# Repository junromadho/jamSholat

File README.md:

# jamSholat
بسم الله الرحمن الرحيم  

Project jam sholat untuk led modul P4.75 dengan menggunakan board berbasis STM32, free to share!

Note: 
Project ini didedikasikan sepenuhnya untuk keperluan amal, silakan memanfaatkan, menyebarkan, dan mengembangkannya. 
Adapun jika anda berniat untuk memanfaatkannya untuk keperluan komersial, harap sisihkan keuntungannya untuk pengembangan lebih lanjut lalu sebarkan ulang pengetahuan tersebut, semoga saja keuntungan yang didapat tidak berhenti hingga rupiah yang terkumpul. tetapi ada keuntungan akhirat yang juga ikut kita tabung.. 

Project ini terdiri dari 3 bagian hardware, software, dan tools
***
## Hardware
Mikrokontroller core yang dipakai adalah varian dari STM32 Bluepill atau Blackpill(belom tested).
Saya biasa memakai varian STM32F103C8T6 dengan papan berwarna biru. 

Dalam kontroler board utama (file: Digital_Praytime_Display_P4.75_v0.9.brd) terdiri dari:
* soket mikrokontroler
* soket untuk HUB08
* soket baterai RTC 
* interface untuk rotary encoder
* interface untuk serial
* interface untuk buzzer
* terminal power

Pada board eksternal (file: External_Battery.brd dan Encoder.brd) terdiri dari:
* soket baterai 
* tombol rotary encoder

board eksternal berfungsi sebagai papan expansi untuk jam sholat yang menggunakan frame tertutup, sehingga board ini bisa diakses diluar 

## Software
Software yang dipakai adalah arduino dengan menggunakan tambahan *hardware* STM32 dari [Arduino STM32](https://github.com/rogerclarkmelbourne/Arduino_STM32). Untuk library saya memakai HUB08 dan RTClock.

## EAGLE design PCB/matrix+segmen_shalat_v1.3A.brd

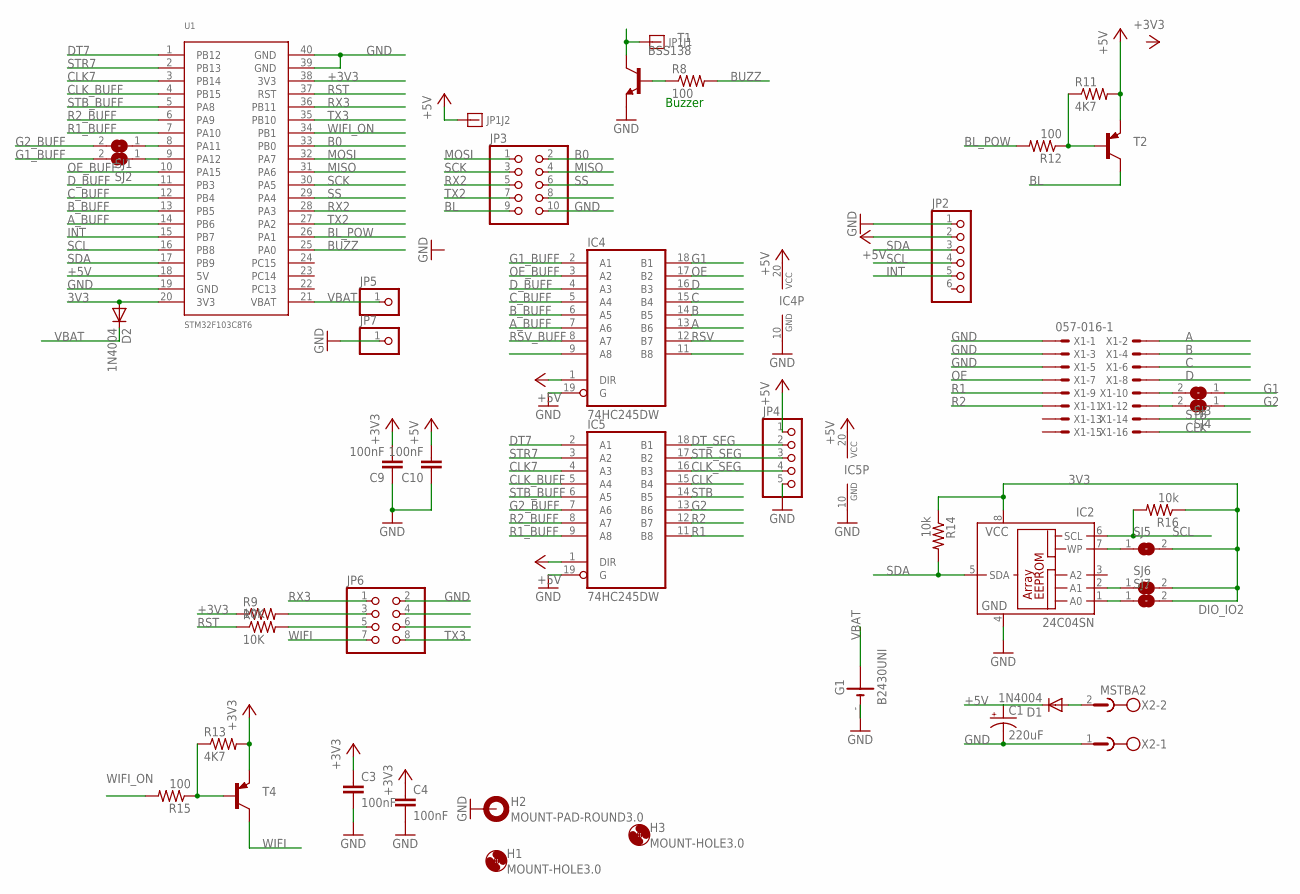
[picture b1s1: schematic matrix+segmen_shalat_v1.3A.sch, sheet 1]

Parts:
C1: 220uF; E3,5-8
C3, C4, C9, C10: 100nF; C0805
D1, D2: 1N4004; DO41-10
G1: B2430UNI
H1, H3: MOUNT-HOLE3.0; 3,0
H2: MOUNT-PAD-ROUND3.0; 3,0-PAD
IC2: 24C04SN; SO-08
IC4, IC5: 74HC245DW; SO20W
JP1: CON2-3.81
JP2: PINHD-1X6; 1X06
JP3: PINHD-2X5; 2X05
JP4: PINHD-1X5; 1X05
JP5, JP7: PINHD-1X1; 1X01
JP6: PINHD-2X4; 2X04
R7, R9: 10K; R0805
R8, R12, R15: 100; R0805
R11, R13: 4K7; R0805
R14, R16: 10k; R0805
SJ1, SJ2, SJ3, SJ4, SJ5, SJ6, SJ7: SJ
T1: BSS138; SOT23-BEC
T2, T4: -PNP-TO126V; TO126V
U1: STM32F103C8T6; STM32F103
X1: 057-016-1
X2: MSTBA2

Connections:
3V3: D2.A, IC2.8 (VCC), R14.1, R16.1, SJ5.2, SJ6.2, SJ7.2, U1.20 (3V3)
+3V3: C3.1, C4.1, C9.2, R9.1, R13.2, T4.1 (E), U1.38 (3V3)
+5V: C1.+, C10.2, D1.C, IC4.1 (DIR), IC4.20 (VCC), IC5.1 (DIR), IC5.20 (VCC), JP1.2, JP2.2, JP4.1, R11.2, T2.1 (E), U1.18 (5V)
A: IC4.13 (B6), X1.2
A_BUFF: IC4.7 (A6), U1.14 (PB6)
B: IC4.14 (B5), X1.4
B0: JP3.2, U1.33 (PB0)
BL: JP3.9, T2.2 (C)
BL_POW: R12.2, U1.26 (PA1)
BUZZ: R8.2, U1.25 (PA0)
B_BUFF: IC4.6 (A5), U1.13 (PB5)
C: IC4.15 (B4), X1.6
CLK: IC5.15 (B4), X1.16
CLK7: IC5.4 (A3), U1.3 (PB14)
CLK_BUFF: IC5.5 (A4), U1.4 (PB15)
CLK_SEG: IC5.16 (B3), JP4.4
C_BUFF: IC4.5 (A4), U1.12 (PB4)
D: IC4.16 (B3), X1.8
DT7: IC5.2 (A1), U1.1 (PB12)
DT_SEG: IC5.18 (B1), JP4.2
D_BUFF: IC4.4 (A3), U1.11 (PB3)
G1: IC4.18 (B1), SJ3.1
G1_BUFF: IC4.2 (A1), SJ2.2
G2: IC5.13 (B6), SJ4.1
G2_BUFF: IC5.7 (A6), SJ1.2
GND: C1.-, C3.2, C4.2, C9.1, C10.1, G1.-, G1.-@1 (-), H2.B3,0, IC2.4 (GND), IC4.10 (GND), IC4.19 (G), IC5.10 (GND), IC5.19 (G), JP2.1, JP3.10, JP4.5, JP6.2, JP7.1, T1.E, U1.19 (GND), U1.39 (GND), U1.40 (GND), X1.1, X1.3, X1.5, X2.1
INT: JP2.5, U1.15 (PB7)
MISO: JP3.4, U1.31 (PA6)
MOSI: JP3.1, U1.32 (PA7)
unnamed: R11.1, R12.1, T2.3 (B)
unnamed: R8.1, T1.B
unnamed: JP1.1, T1.C
unnamed: JP6.3, R9.2
unnamed: IC2.2 (A1), SJ6.1
unnamed: R13.1, R15.1, T4.3 (B)
unnamed: SJ1.1, U1.8 (PA11)
unnamed: SJ2.1, U1.9 (PA12)
unnamed: SJ4.2, X1.12
unnamed: SJ3.2, X1.10
unnamed: IC2.1 (A0), SJ7.1
unnamed: JP6.5, R7.2
unnamed: D1.A, X2.2
unnamed: IC2.7 (WP), SJ5.1
OE: IC4.17 (B2), X1.7
OE_BUFF: IC4.3 (A2), U1.10 (PA15)
R1: IC5.11 (B8), X1.9
R1_BUFF: IC5.9 (A8), U1.7 (PA10)
R2: IC5.12 (B7), X1.11
R2_BUFF: IC5.8 (A7), U1.6 (PA9)
RST: R7.1, U1.37 (RST)
RSV: IC4.12 (B7)
RSV_BUFF: IC4.8 (A7)
RX2: JP3.5, U1.28 (PA3)
RX3: JP6.1, U1.36 (PB11)
SCK: JP3.3, U1.30 (PA5)
SCL: IC2.6 (SCL), JP2.4, R16.2, U1.16 (PB8)
SDA: IC2.5 (SDA), JP2.3, R14.2, U1.17 (PB9)
SS: JP3.6, U1.29 (PA4)
STB: IC5.14 (B5), X1.14
STB_BUFF: IC5.6 (A5), U1.5 (PA8)
STR7: IC5.3 (A2), U1.2 (PB13)
STR_SEG: IC5.17 (B2), JP4.3
TX2: JP3.7, U1.27 (PA2)
TX3: JP6.8, U1.35 (PB10)
VBAT: D2.C, G1.+@4 (+), JP5.1, U1.21 (VBAT)
WIFI: JP6.7, T4.2 (C)
WIFI_ON: R15.2, U1.34 (PB1)

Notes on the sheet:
Buzzer

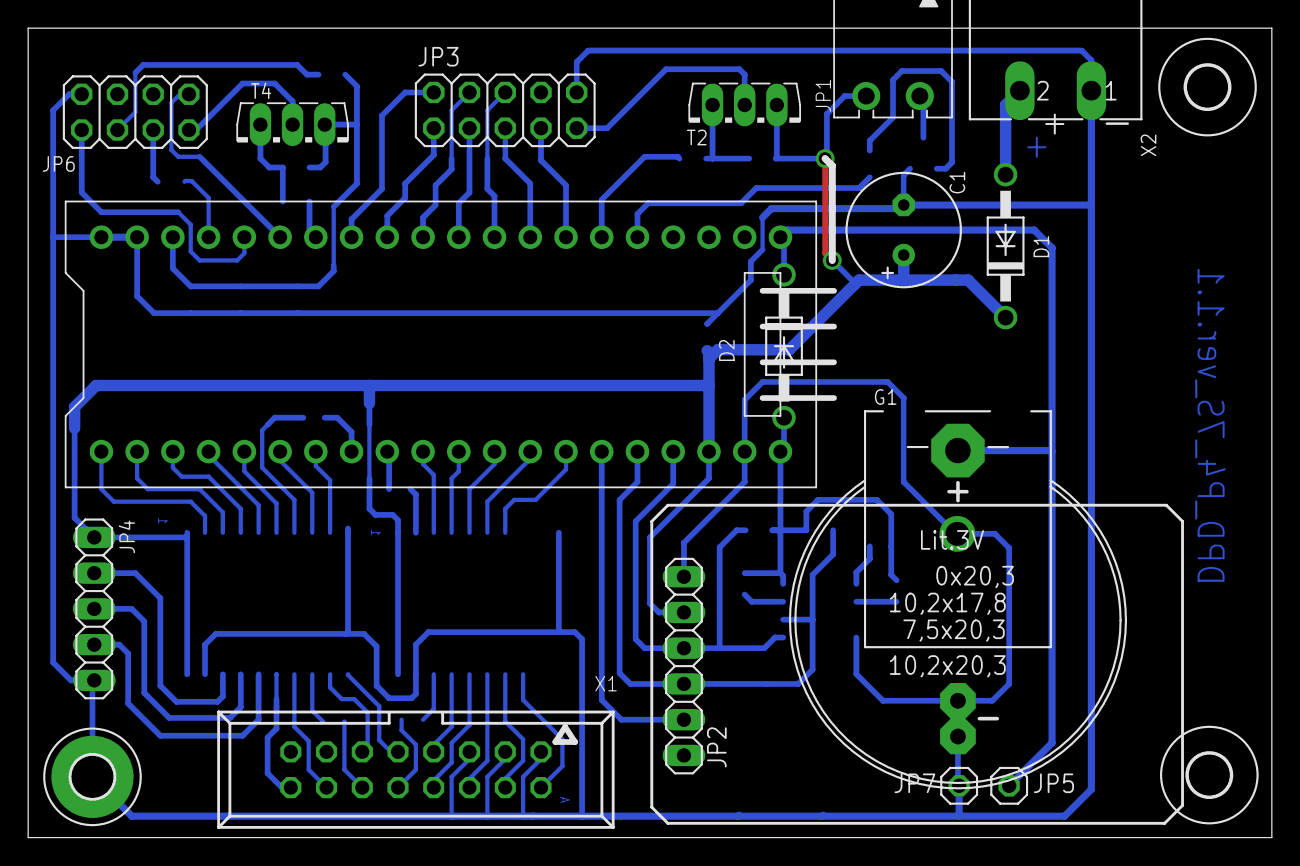
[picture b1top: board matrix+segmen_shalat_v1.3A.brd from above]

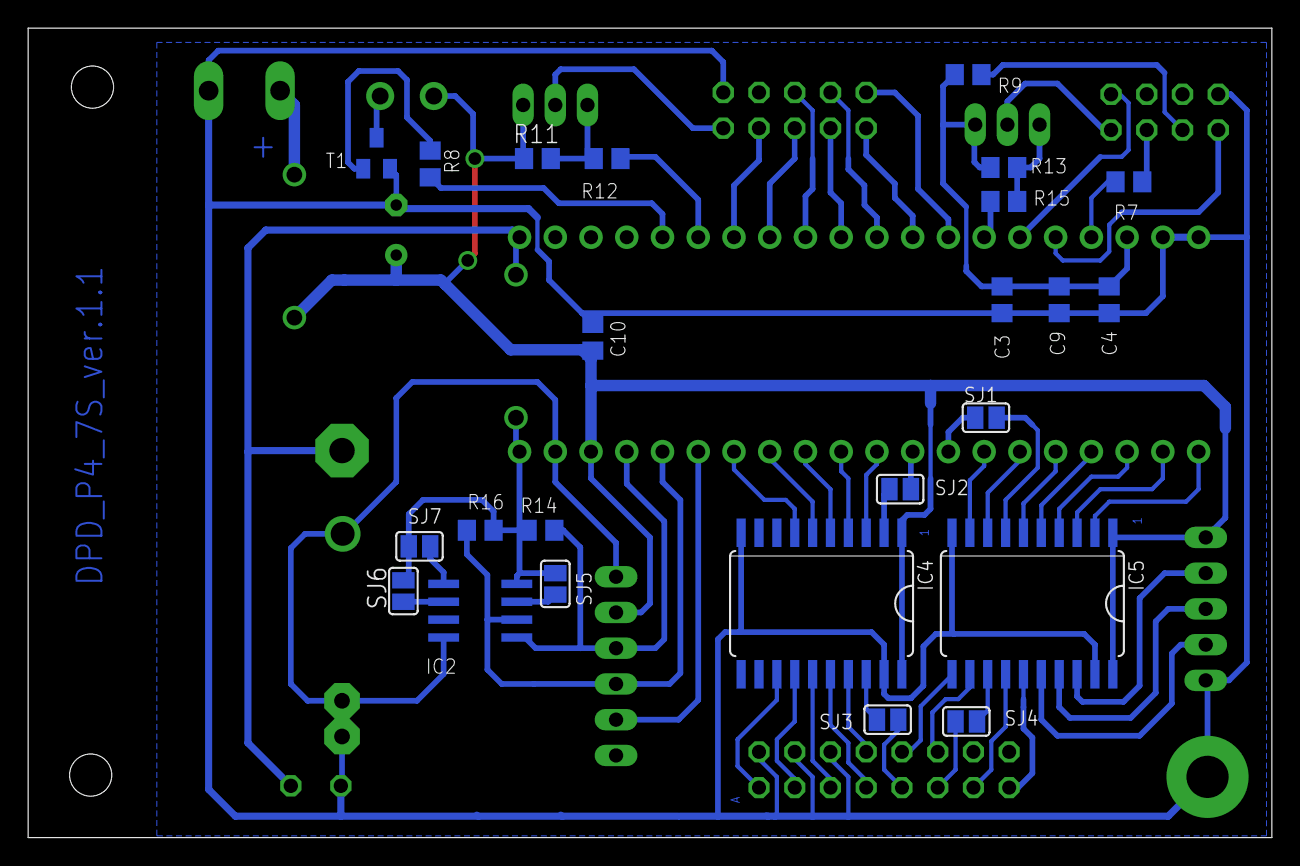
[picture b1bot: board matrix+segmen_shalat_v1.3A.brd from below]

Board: 2 copper layers, 88.4 x 57.5 mm, 43 parts (24 on the bottom side), 65 nets.

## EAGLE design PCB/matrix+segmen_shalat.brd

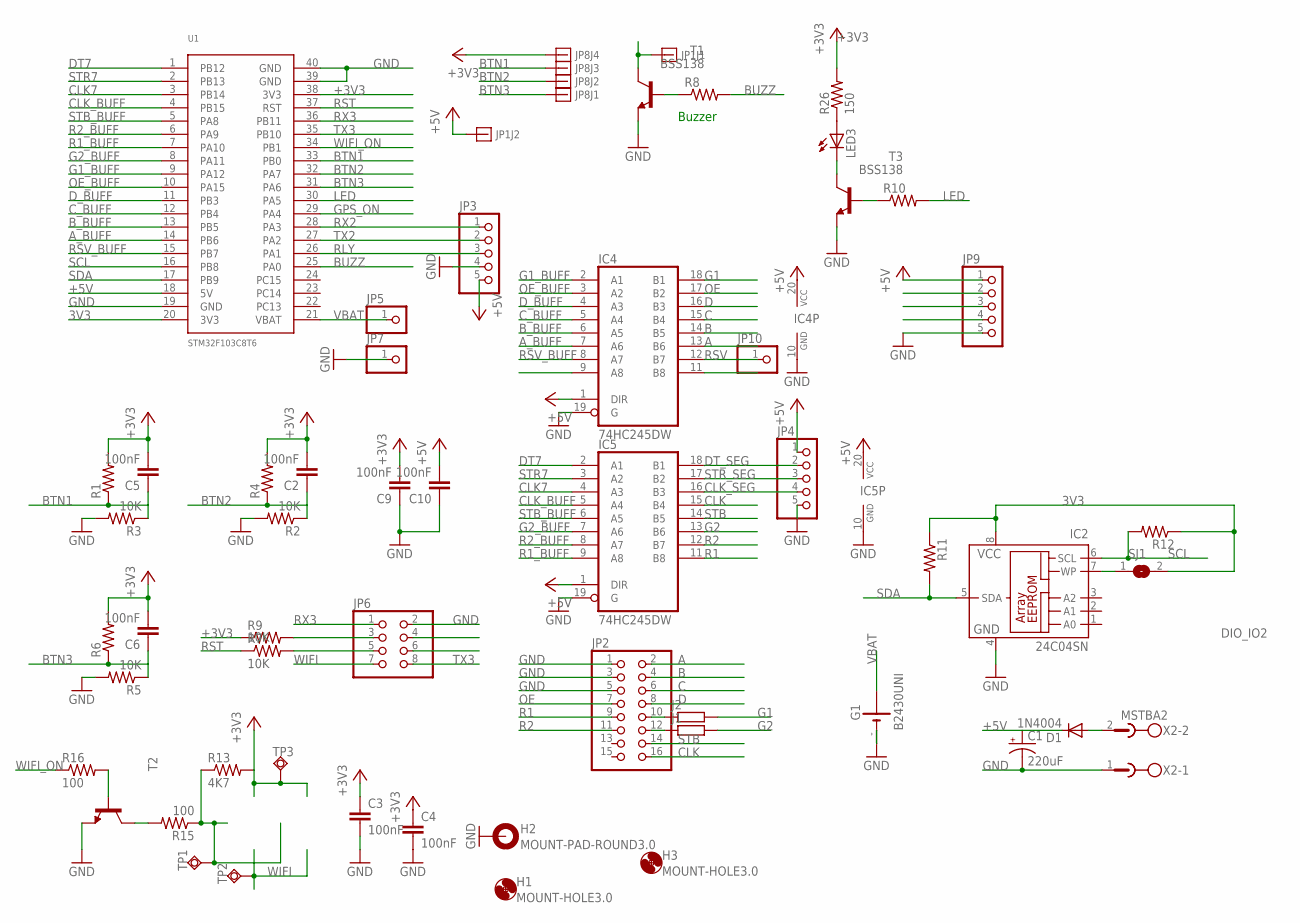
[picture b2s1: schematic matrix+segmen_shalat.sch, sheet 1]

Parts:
C1: 220uF; E3,5-8
C2, C3, C4, C5, C6, C9, C10: 100nF; C0805
D1: 1N4004; DO41-10
G1: B2430UNI
H1, H3: MOUNT-HOLE3.0; 3,0
H2: MOUNT-PAD-ROUND3.0; 3,0-PAD
IC2: 24C04SN; SO-08
IC4, IC5: 74HC245DW; SO20W
J1, J2: R-EU_R0402; R0402
JP1: CON2-3.81
JP2: PINHD-2X8; 2X08
JP3, JP4, JP9: PINHD-1X5; 1X05
JP5, JP7, JP10: PINHD-1X1; 1X01
JP6: PINHD-2X4; 2X04
JP8: CON4-3.81
LED3: LED3MM
R1, R4, R6: R-US_0204/2V; 0204V
R2, R3, R5: 10K; M0805
R7, R9: 10K; R0805
R8, R10, R11, R12: R-US_R0805; R0805
R13: 4K7; R0805
R15, R16: 100; R0805
R26: 150; R0805
SJ1: SJ
T1, T3: BSS138; SOT23-BEC
T2: MMBT2222ALT1-NPN-SOT23-BEC; SOT23-BEC
TP1, TP2, TP3: TPSQPAD1-13Y; P1-13Y
U1: STM32F103C8T6; STM32F103
X2: MSTBA2

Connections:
3V3: IC2.8 (VCC), R11.1, R12.1, SJ1.2, U1.20 (3V3)
+3V3: C2.2, C3.1, C4.1, C5.2, C6.2, C9.2, JP8.4, R1.2, R4.2, R6.2, R9.1, R13.2, R26.2, TP3.TP, U1.38 (3V3)
+5V: C1.+, C10.2, D1.C, IC4.1 (DIR), IC4.20 (VCC), IC5.1 (DIR), IC5.20 (VCC), JP1.2, JP3.5, JP4.1, JP9.1, U1.18 (5V)
A: IC4.13 (B6), JP2.2
A_BUFF: IC4.7 (A6), U1.14 (PB6)
B: IC4.14 (B5), JP2.4
BTN1: C5.1, JP8.3, R1.1, R3.1, U1.33 (PB0)
BTN2: C2.1, JP8.2, R2.1, R4.1, U1.32 (PA7)
BTN3: C6.1, JP8.1, R5.1, R6.1, U1.31 (PA6)
BUZZ: R8.2, U1.25 (PA0)
B_BUFF: IC4.6 (A5), U1.13 (PB5)
C: IC4.15 (B4), JP2.6
CLK: IC5.15 (B4), JP2.16
CLK7: IC5.4 (A3), U1.3 (PB14)
CLK_BUFF: IC5.5 (A4), U1.4 (PB15)
CLK_SEG: IC5.16 (B3), JP4.4
C_BUFF: IC4.5 (A4), U1.12 (PB4)
D: IC4.16 (B3), JP2.8
DT7: IC5.2 (A1), U1.1 (PB12)
DT_SEG: IC5.18 (B1), JP4.2
D_BUFF: IC4.4 (A3), U1.11 (PB3)
G1: IC4.18 (B1), J2.2
G1_BUFF: IC4.2 (A1), U1.9 (PA12)
G2: IC5.13 (B6), J1.2
G2_BUFF: IC5.7 (A6), U1.8 (PA11)
GND: C1.-, C3.2, C4.2, C9.1, C10.1, G1.-, G1.-@1 (-), H2.B3,0, IC2.4 (GND), IC4.10 (GND), IC4.19 (G), IC5.10 (GND), IC5.19 (G), JP2.1, JP2.3, JP2.5, JP3.4, JP4.5, JP6.2, JP7.1, JP9.5, R2.2, R3.2, R5.2, T1.E, T2.E, T3.E, U1.19 (GND), U1.39 (GND), U1.40 (GND), X2.1
GPS_ON: U1.29 (PA4)
LED: R10.2, U1.30 (PA5)
unnamed: J1.1, JP2.12
unnamed: LED3.K (C), T3.C
unnamed: R10.1, T3.B
unnamed: R8.1, T1.B
unnamed: JP1.1, T1.C
unnamed: JP6.3, R9.2
unnamed: J2.1, JP2.10
unnamed: R13.1, R15.1, TP1.TP
unnamed: R15.2, T2.C
unnamed: JP6.5, R7.2
unnamed: R16.2, T2.B
unnamed: LED3.A, R26.1
unnamed: D1.A, X2.2
unnamed: IC2.7 (WP), SJ1.1
OE: IC4.17 (B2), JP2.7
OE_BUFF: IC4.3 (A2), U1.10 (PA15)
R1: IC5.11 (B8), JP2.9
R1_BUFF: IC5.9 (A8), U1.7 (PA10)
R2: IC5.12 (B7), JP2.11
R2_BUFF: IC5.8 (A7), U1.6 (PA9)
RLY: JP3.3, U1.26 (PA1)
RST: R7.1, U1.37 (RST)
RSV: IC4.12 (B7), JP10.1
RSV_BUFF: IC4.8 (A7), U1.15 (PB7)
RX2: JP3.1, U1.28 (PA3)
RX3: JP6.1, U1.36 (PB11)
SCL: IC2.6 (SCL), R12.2, U1.16 (PB8)
SDA: IC2.5 (SDA), R11.2, U1.17 (PB9)
STB: IC5.14 (B5), JP2.14
STB_BUFF: IC5.6 (A5), U1.5 (PA8)
STR7: IC5.3 (A2), U1.2 (PB13)
STR_SEG: IC5.17 (B2), JP4.3
TX2: JP3.2, U1.27 (PA2)
TX3: JP6.8, U1.35 (PB10)
VBAT: G1.+@4 (+), JP5.1, U1.21 (VBAT)
WIFI: JP6.7, TP2.TP
WIFI_ON: R16.1, U1.34 (PB1)

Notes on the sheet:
Buzzer

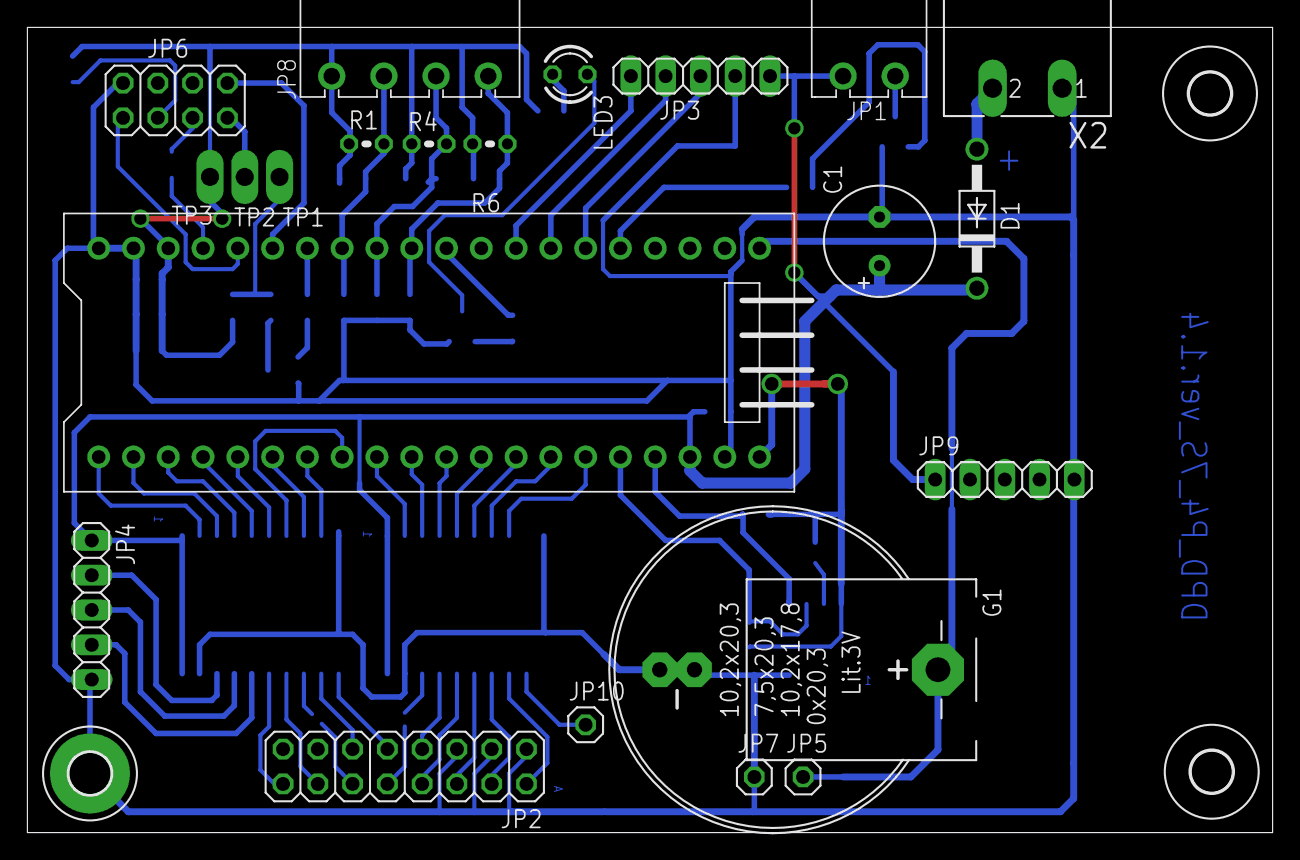
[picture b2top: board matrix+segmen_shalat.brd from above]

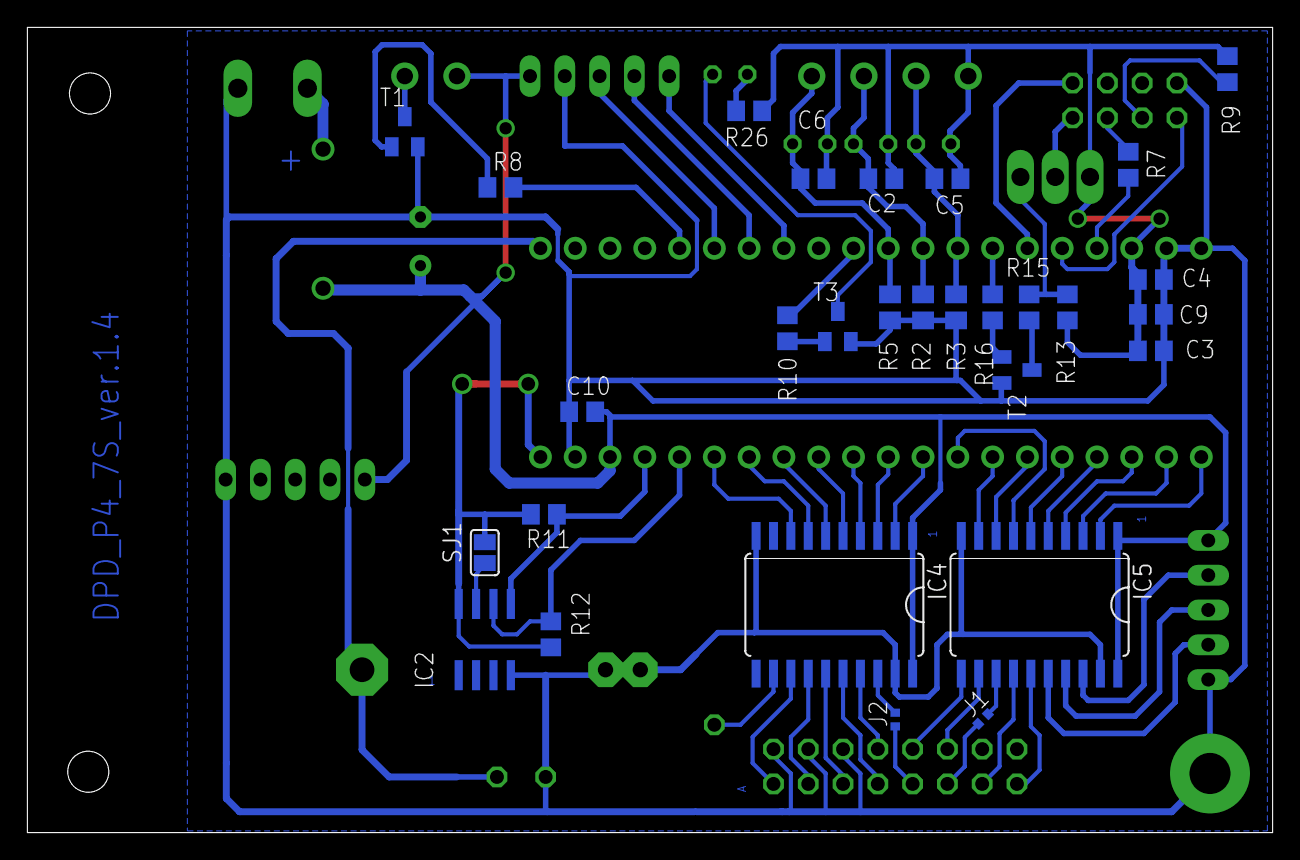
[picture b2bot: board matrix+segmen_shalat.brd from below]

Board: 2 copper layers, 90.9 x 58.8 mm, 54 parts (29 on the bottom side), 64 nets.

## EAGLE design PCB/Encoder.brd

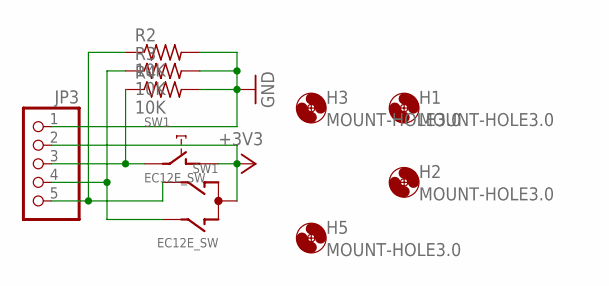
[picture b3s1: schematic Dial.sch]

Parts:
H1, H2, H3, H5: MOUNT-HOLE3.0; 3,0
JP3: PINHD-1X5; 1X05
R2, R3, R4: 10K; R0805
SW1: EC12E_SW; ALPS_EC12E_SW

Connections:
+3V3: JP3.2, SW1.C, SW1.D (1)
GND: JP3.1, R2.2, R3.2, R4.2
unnamed: JP3.4, R3.1, SW1.B
unnamed: JP3.5, R2.1, SW1.A
unnamed: JP3.3, R4.1, SW1.E (2)

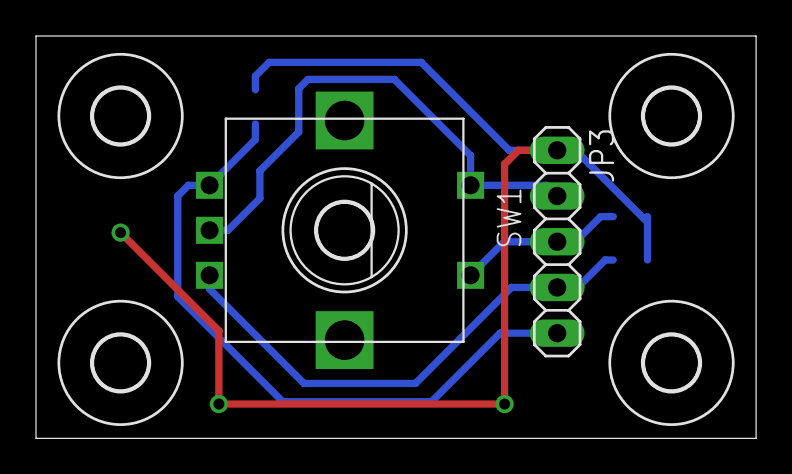
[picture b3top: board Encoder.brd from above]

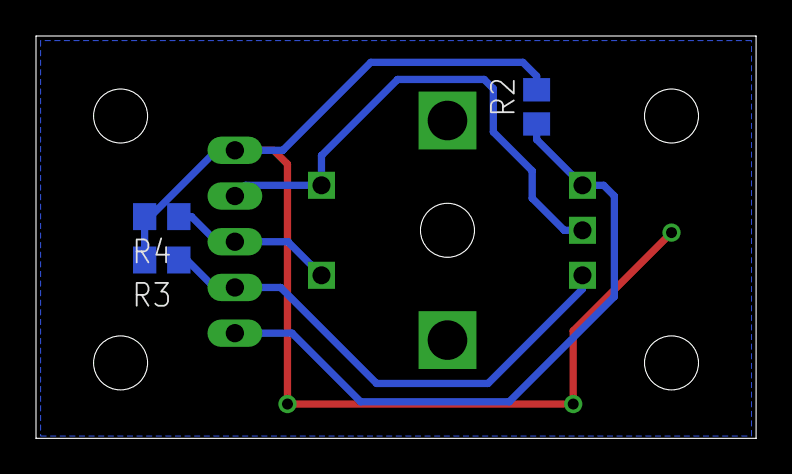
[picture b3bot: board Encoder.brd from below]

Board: 2 copper layers, 40.0 x 22.4 mm, 10 parts (3 on the bottom side), 5 nets.

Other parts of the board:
H4: MOUNT-HOLE3.0; 3,0

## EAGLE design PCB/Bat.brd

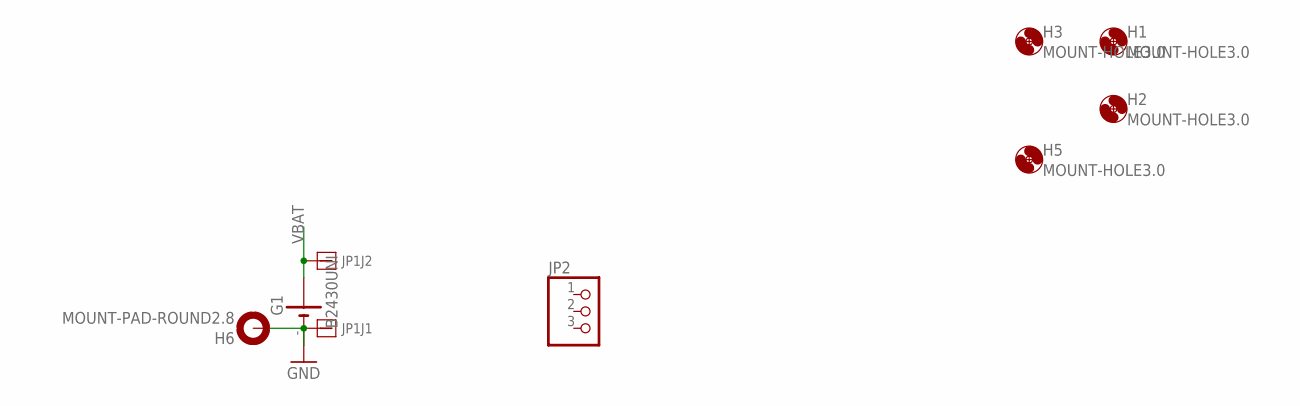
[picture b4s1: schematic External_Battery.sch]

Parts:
G1: B2430UNI
H1, H2, H3, H5: MOUNT-HOLE3.0; 3,0
H6: MOUNT-PAD-ROUND2.8; 2,8-PAD
JP1: CON2-3.81
JP2: PINHD-1X3; 1X03

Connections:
GND: G1.-, G1.-@1 (-), H6.B2,8, JP1.1
VBAT: G1.+@4 (+), JP1.2

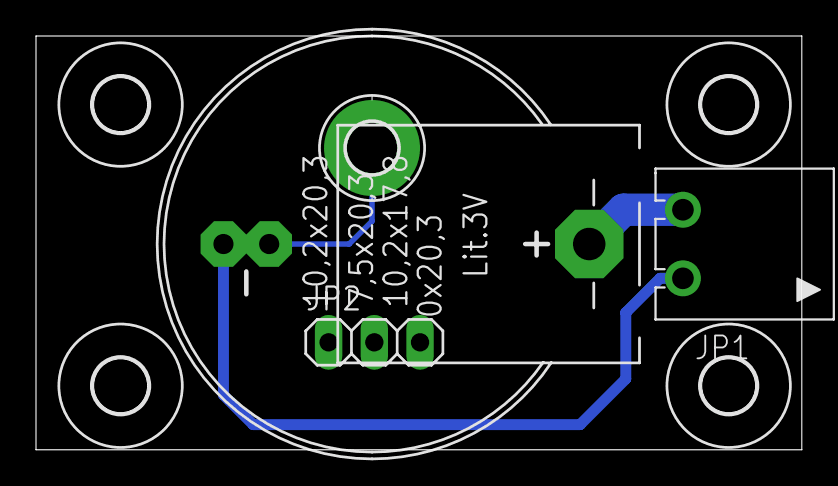
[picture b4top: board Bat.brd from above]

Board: 2 copper layers, 42.5 x 23.0 mm, 8 parts (0 on the bottom side), 2 nets.

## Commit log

2021-01-07 PCB untuk versi 1.4, perubahan code pin harus disesuaikan
2021-01-16 add some code and pcb
2021-01-25 Melengkapi resource
2021-08-12 layout PCB utk jam sholat p4.75 ver.1.3a
2022-01-04 Add code matrix 1 module
2022-01-04 Coding utk esp8266 webserver config
2023-07-22 just try
